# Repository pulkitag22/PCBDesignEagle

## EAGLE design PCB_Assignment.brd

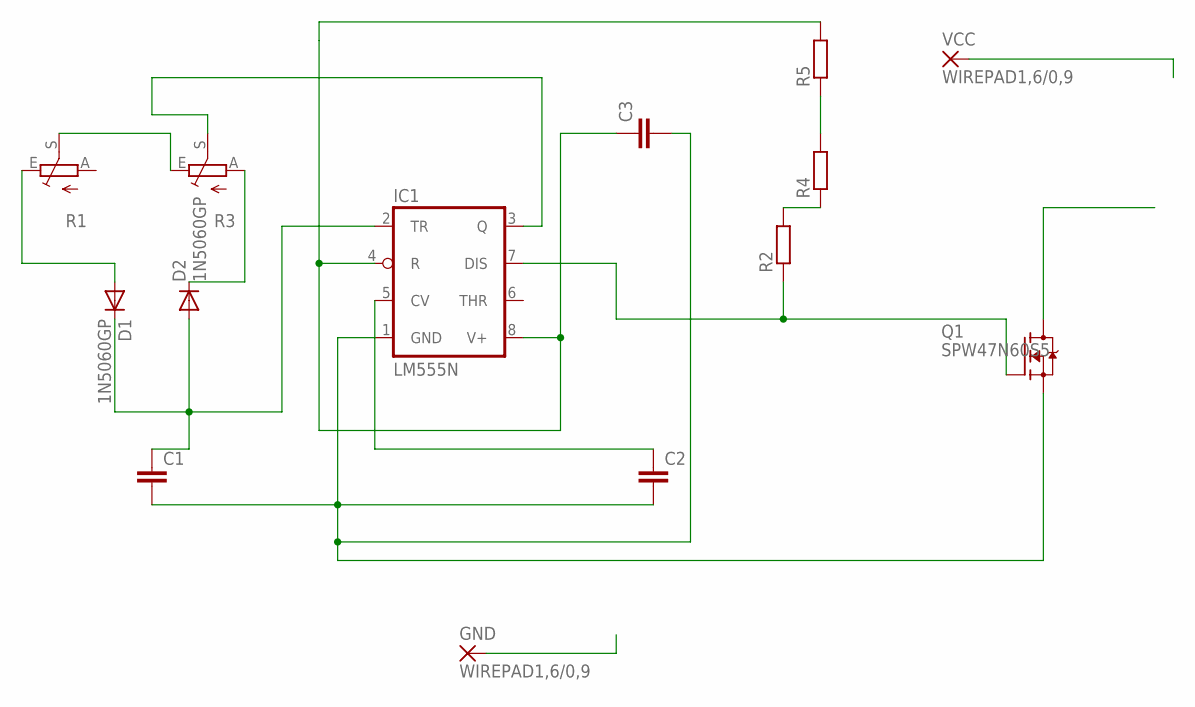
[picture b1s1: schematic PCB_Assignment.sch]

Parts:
C1, C2, C3: C2.5/2; C2.5-2
D1, D2: 1N5060GP; DO15-12
GND: WIREPAD1,6/0,9; 1,6/0,9
IC1: LM555N; DIL08
Q1: SPW47N60S5; P-TO247
R1, R3: TRIM_EU-B64Y; B64Y
R2, R4, R5: R0204/7; 0204/7
VCC: WIREPAD1,6/0,9; 1,6/0,9

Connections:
GND: C1.2, C2.2, C3.2, GND.1, IC1.1 (GND), Q1.3 (S)
unnamed: IC1.7 (DIS), Q1.1 (G), R2.1
unnamed: C1.1, D1.C, D2.A, IC1.2 (TR)
unnamed: D2.C, R3.A
unnamed: D1.A, R1.E
unnamed: IC1.3 (Q), R3.S
unnamed: R1.S, R3.E
unnamed: C2.1, IC1.5 (CV)
unnamed: R2.2, R4.1
unnamed: R4.2, R5.1
VCC: C3.1, IC1.4 (R), IC1.8 (V+), R5.2, VCC.1

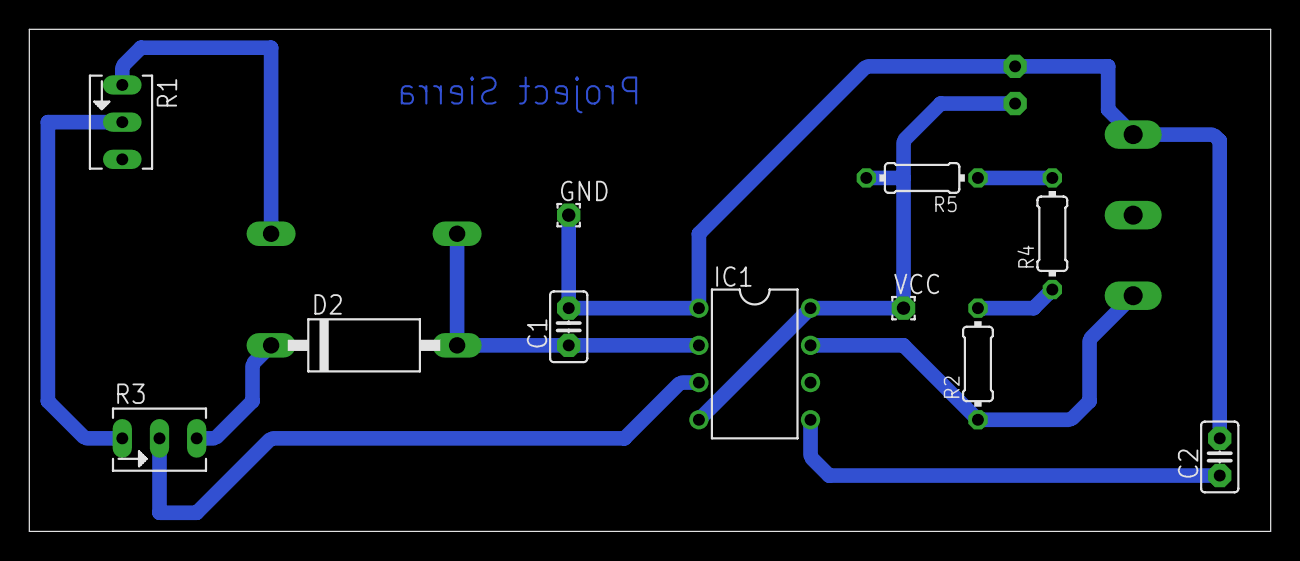
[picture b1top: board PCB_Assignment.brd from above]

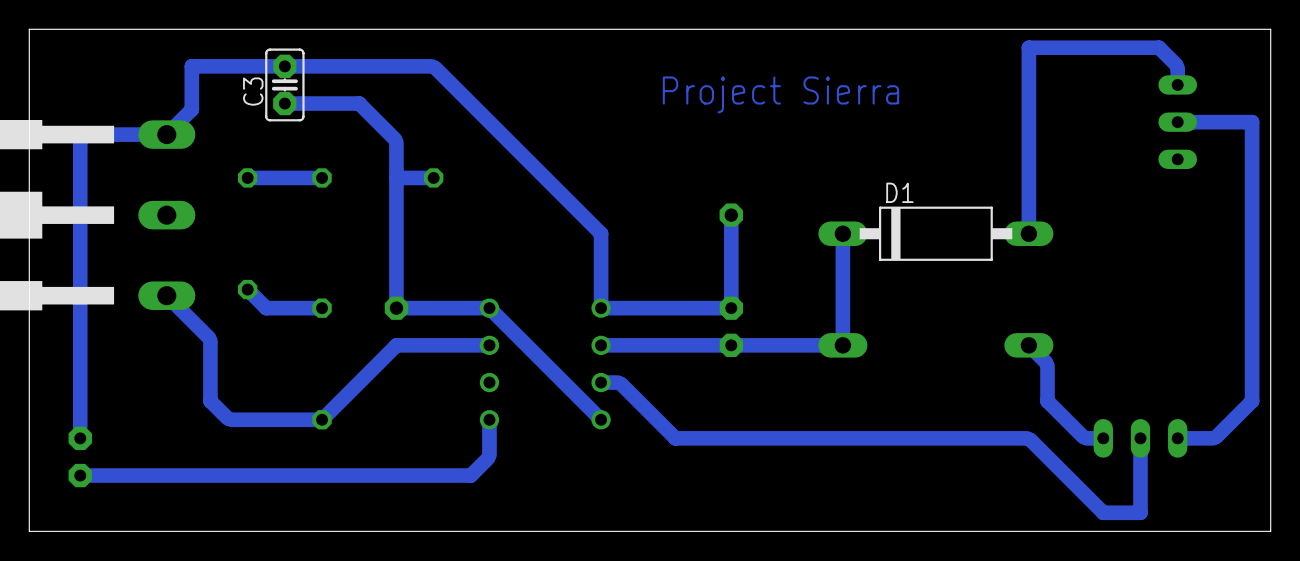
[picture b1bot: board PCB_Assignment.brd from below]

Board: 2 copper layers, 84.8 x 34.3 mm, 14 parts (3 on the bottom side), 11 nets.
